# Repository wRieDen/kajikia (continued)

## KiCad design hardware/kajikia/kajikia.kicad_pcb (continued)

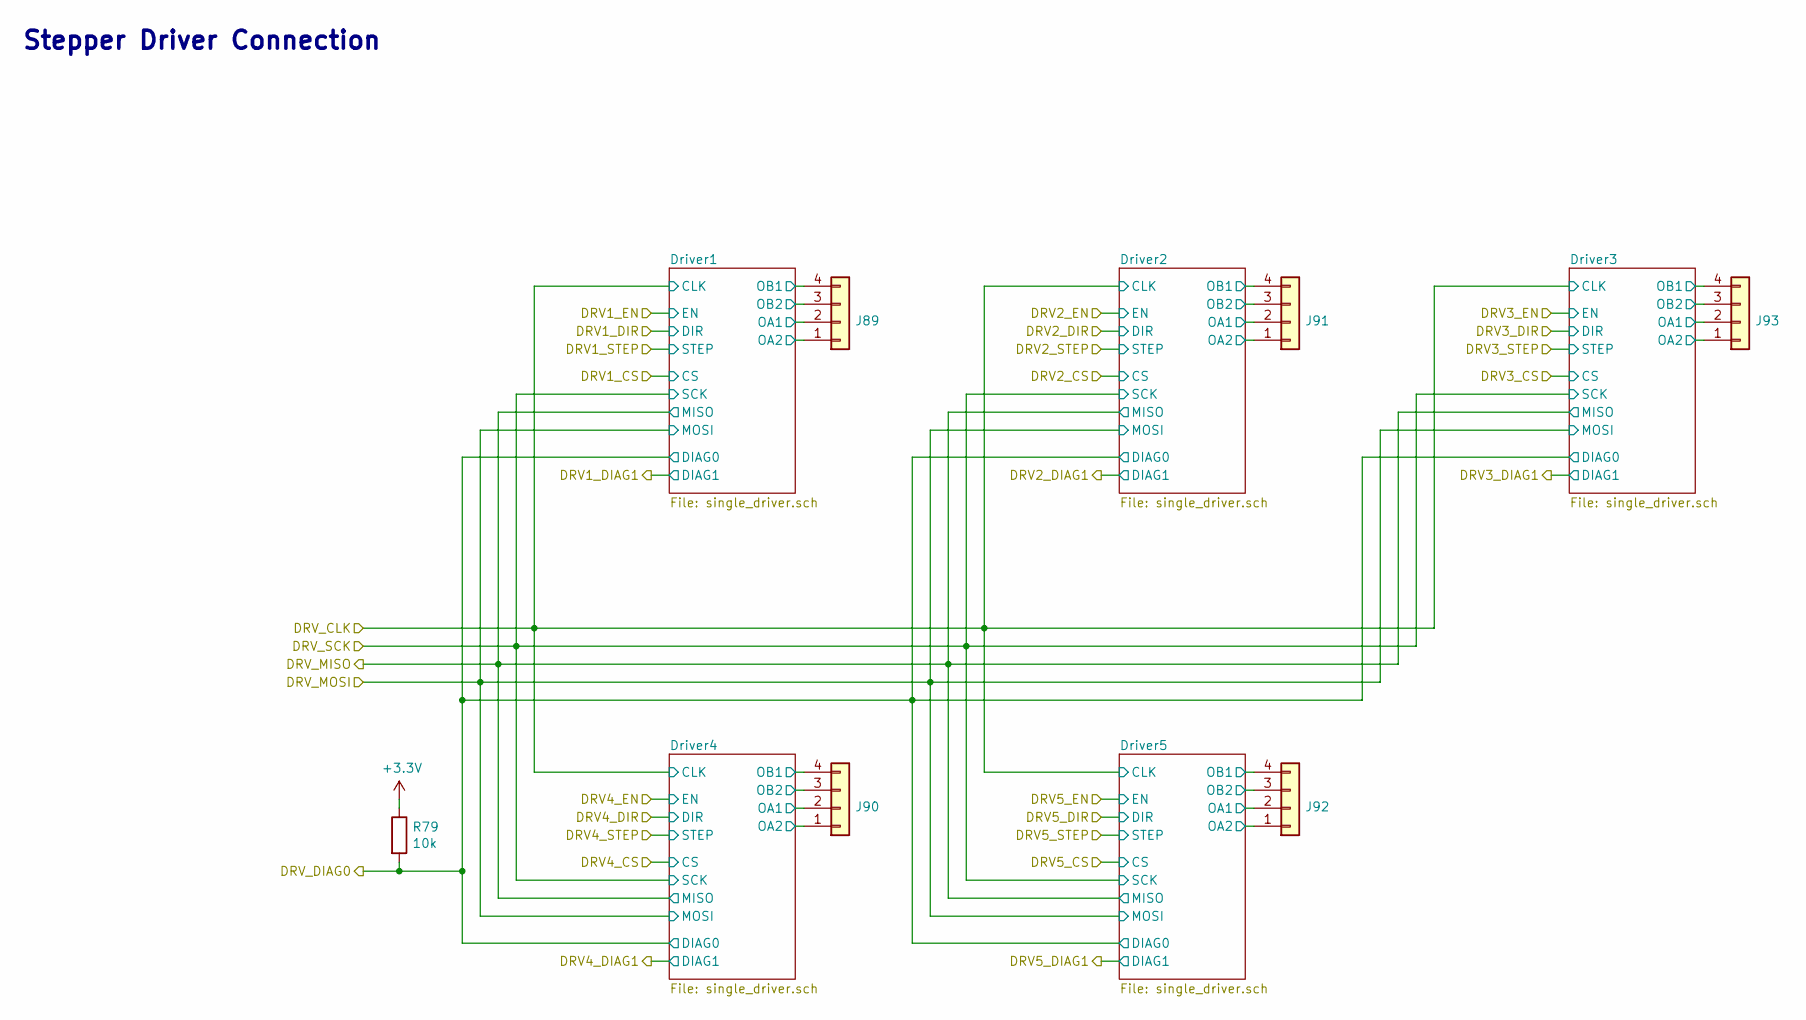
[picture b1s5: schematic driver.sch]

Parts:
J89, J90, J91, J92, J93: Conn_01x04; JST_XH_4P
R79: 10k; 0603_RES

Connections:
+3V3: R79.1; also elsewhere on the board
/Stepper Driver/DRV_DIAG0: R79.2; also elsewhere on the board
/Stepper Driver/Driver1/OA1: J89.2; also elsewhere on the board
/Stepper Driver/Driver1/OA2: J89.1; also elsewhere on the board
/Stepper Driver/Driver1/OB1: J89.4; also elsewhere on the board
/Stepper Driver/Driver1/OB2: J89.3; also elsewhere on the board
/Stepper Driver/Driver2/OA1: J91.2; also elsewhere on the board
/Stepper Driver/Driver2/OA2: J91.1; also elsewhere on the board
/Stepper Driver/Driver2/OB1: J91.4; also elsewhere on the board
/Stepper Driver/Driver2/OB2: J91.3; also elsewhere on the board
/Stepper Driver/Driver3/OA1: J93.2; also elsewhere on the board
/Stepper Driver/Driver3/OA2: J93.1; also elsewhere on the board
/Stepper Driver/Driver3/OB1: J93.4; also elsewhere on the board
/Stepper Driver/Driver3/OB2: J93.3; also elsewhere on the board
/Stepper Driver/Driver4/OA1: J90.2; also elsewhere on the board
/Stepper Driver/Driver4/OA2: J90.1; also elsewhere on the board
/Stepper Driver/Driver4/OB1: J90.4; also elsewhere on the board
/Stepper Driver/Driver4/OB2: J90.3; also elsewhere on the board
/Stepper Driver/Driver5/OA1: J92.2; also elsewhere on the board
/Stepper Driver/Driver5/OA2: J92.1; also elsewhere on the board
/Stepper Driver/Driver5/OB1: J92.4; also elsewhere on the board
/Stepper Driver/Driver5/OB2: J92.3; also elsewhere on the board

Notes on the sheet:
Stepper Driver Connection

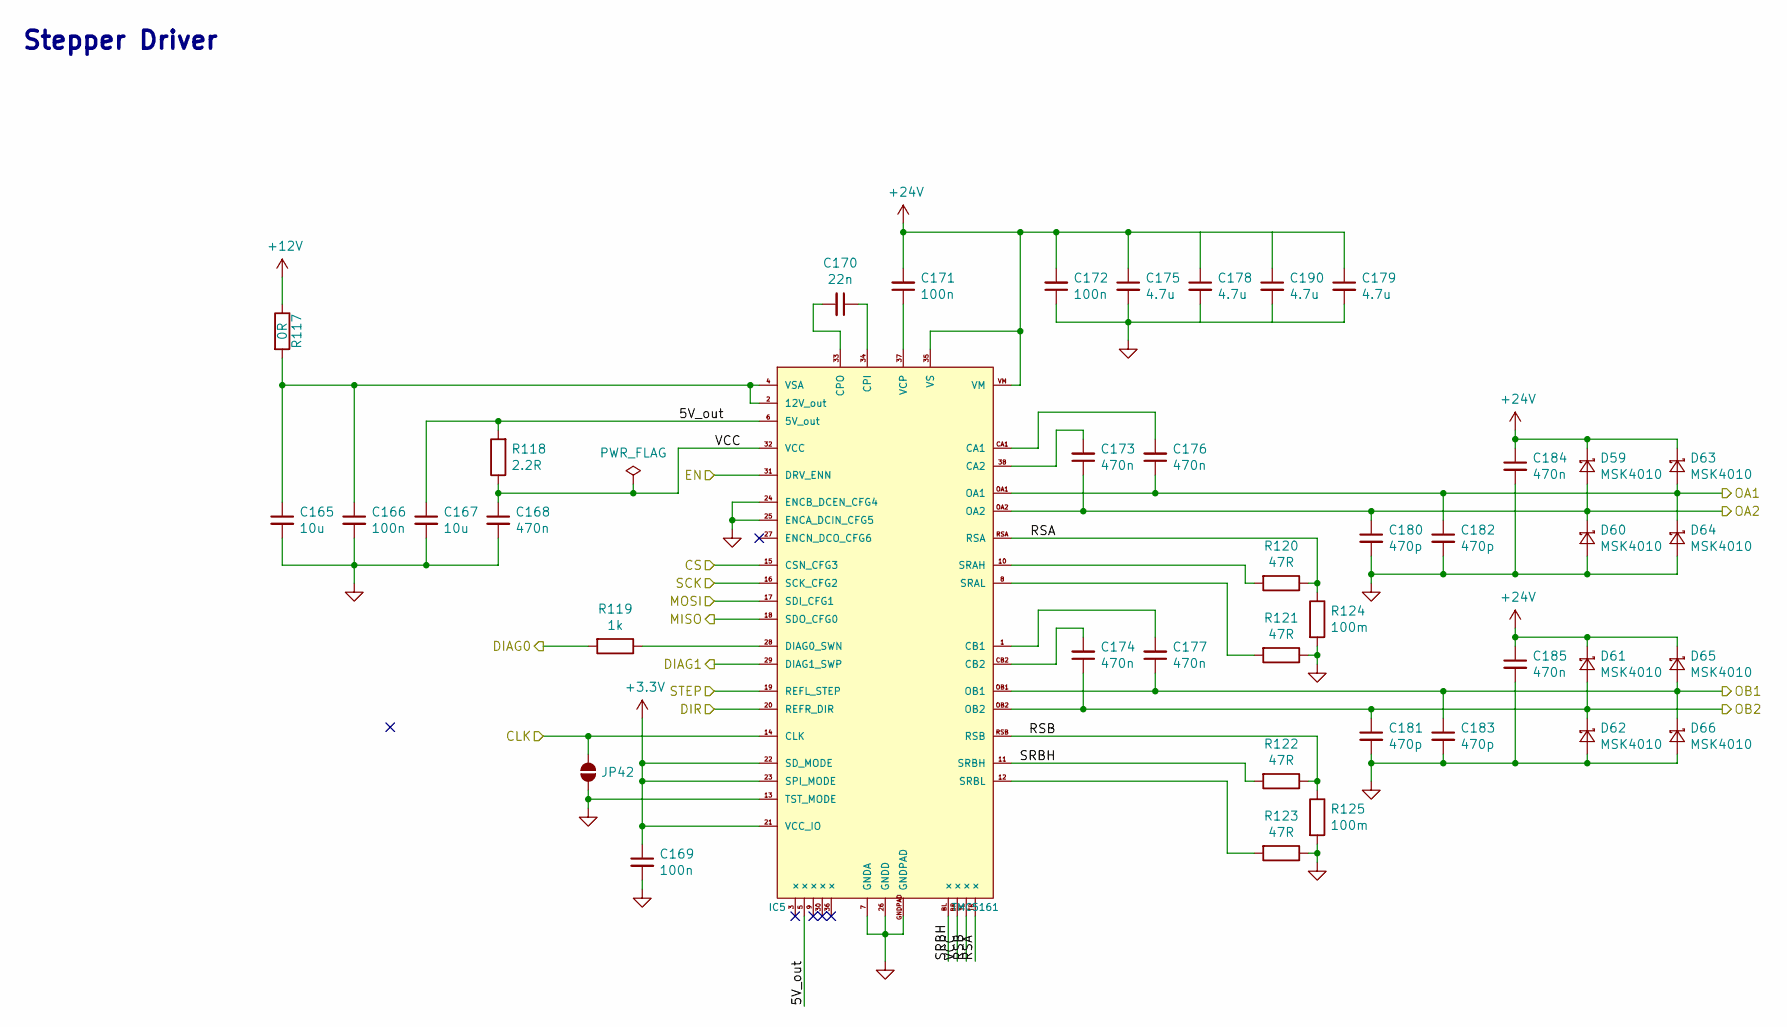
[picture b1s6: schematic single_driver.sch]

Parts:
C81, C83: 10u; 0603_CAP
C82, C85, C87, C88: 100n; 0603_CAP
C84, C89, C90, C92, C93, C100, C101: 470n; 0603_CAP
C86: 22n; 0603_CAP
C91, C94, C95, C186: 4.7u; 1210_CAP
C96, C97, C98, C99: 470p; 0603_CAP
D27, D28, D29, D30, D31, D32, D33, D34: MSK4010; SOD-523_DIODE
IC1: TMC5161; QFN42L
JP38: SolderJumper_2_Open; Solder Jumper 2P
R81: 0R; 0603_RES
R82: 2.2R; 0603_RES
R83: 1k; 0603_RES
R84, R85, R86, R87: 47R; 0603_RES
R88, R89: 100m; 1206_RES

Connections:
+3V3: C85.1, IC1.21 (VCC_IO), IC1.22 (SD_MODE), IC1.23 (SPI_MODE); also elsewhere on the board
+12V: R81.1; also elsewhere on the board
+24V: C87.2, C88.2, C91.1, C94.1, C95.1, C100.1, C101.1, C186.1, D27.1 (K), D29.1 (K), D31.1 (K), D33.1 (K), IC1.35 (VS), IC1.VM; also elsewhere on the board
/DRV1_CS: IC1.15 (CSN_CFG3); also elsewhere on the board
/DRV1_DIR: IC1.20 (REFR_DIR); also elsewhere on the board
/DRV1_EN: IC1.31 (DRV_ENN); also elsewhere on the board
/DRV1_STEP: IC1.19 (REFL_STEP); also elsewhere on the board
/DRV_CLK: IC1.14 (CLK), JP38.1 (A); also elsewhere on the board
/DRV_MISO: IC1.18 (SDO_CFG0); also elsewhere on the board
/DRV_MOSI: IC1.17 (SDI_CFG1); also elsewhere on the board
/DRV_SCK: IC1.16 (SCK_CFG2); also elsewhere on the board
/Stepper Driver/DRV1_DIAG1: IC1.29 (DIAG1_SWP); also elsewhere on the board
/Stepper Driver/DRV_DIAG0: R83.2; also elsewhere on the board
/Stepper Driver/Driver1/5V_out: C83.1, IC1.5 (×), IC1.6 (5V_out), R82.2
/Stepper Driver/Driver1/OA1: C92.1, C98.1, D31.2 (A), D32.1 (K), IC1.OA1; also elsewhere on the board
/Stepper Driver/Driver1/OA2: C89.1, C96.1, D27.2 (A), D28.1 (K), IC1.OA2; also elsewhere on the board
/Stepper Driver/Driver1/OB1: C93.1, C99.1, D33.2 (A), D34.1 (K), IC1.OB1; also elsewhere on the board
/Stepper Driver/Driver1/OB2: C90.1, C97.1, D29.2 (A), D30.1 (K), IC1.OB2; also elsewhere on the board
/Stepper Driver/Driver1/RSA: IC1.RSA, IC1.TR (×), R84.1, R88.1
/Stepper Driver/Driver1/RSB: IC1.RSB, IC1.TL (×), R86.1, R89.1
/Stepper Driver/Driver1/SRBH: IC1.11 (SRBH), IC1.BL (×), R86.2
/Stepper Driver/Driver1/VCC: C84.1, IC1.32 (VCC), IC1.BR (×), R82.1
GND: C81.2, C82.2, C83.2, C84.2, C85.2, C88.1, C91.2, C94.2, C95.2, C96.2, C97.2, C98.2, C99.2, C100.2, C101.2, C186.2, D28.2 (A), D30.2 (A), D32.2 (A), D34.2 (A), IC1.7 (GNDA), IC1.13 (TST_MODE), IC1.24 (ENCB_DCEN_CFG4), IC1.25 (ENCA_DCIN_CFG5), IC1.26 (GNDD), IC1.GNDPAD, JP38.2 (B), R85.1, R87.1, R88.2, R89.2; also elsewhere on the board
unnamed: C81.1, C82.1, IC1.2 (12V_out), IC1.4 (VSA), R81.2
unnamed: C86.1, IC1.34 (CPI)
unnamed: C86.2, IC1.33 (CPO)
unnamed: C87.1, IC1.37 (VCP)
unnamed: C89.2, IC1.38 (CA2)
unnamed: C90.2, IC1.CB2
unnamed: C92.2, IC1.CA1
unnamed: C93.2, IC1.1 (CB1)
unnamed: IC1.8 (SRAL), R85.2
unnamed: IC1.10 (SRAH), R84.2
unnamed: IC1.12 (SRBL), R87.2
unnamed: IC1.28 (DIAG0_SWN), R83.1

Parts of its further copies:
C102, C104, C123, C125, C144, C146, C165, C167: 10u; 0603_CAP
C103, C106, C108, C109, C124, C127, C129, C130, C145, C148, C150, C151, C166, C169, C171, C172: 100n; 0603_CAP
C105, C110, C111, C113, C114, C121, C122, C126, C131, C132, C134, C135, C142, C143, C147, C152, C153, C155, C156, C163, C164, C168, C173, C174, C176, C177, C184, C185: 470n; 0603_CAP
C107, C128, C149, C170: 22n; 0603_CAP
C112, C115, C116, C133, C136, C137, C154, C157, C158, C175, C178, C179, C187, C188, C189, C190: 4.7u; 1210_CAP
C117, C118, C119, C120, C138, C139, C140, C141, C159, C160, C161, C162, C180, C181, C182, C183: 470p; 0603_CAP
D35, D36, D37, D38, D39, D40, D41, D42, D43, D44, D45, D46, D47, D48, D49, D50, D51, D52, D53, D54, D55, D56, D57, D58, D59, D60, D61, D62, D63, D64, D65, D66: MSK4010; SOD-523_DIODE
IC2, IC3, IC4, IC5: TMC5161; QFN42L
JP39, JP40, JP41, JP42: SolderJumper_2_Open; Solder Jumper 2P
R90, R99, R108, R117: 0R; 0603_RES
R91, R100, R109, R118: 2.2R; 0603_RES
R92, R101, R110, R119: 1k; 0603_RES
R93, R94, R95, R96, R102, R103, R104, R105, R111, R112, R113, R114, R120, R121, R122, R123: 47R; 0603_RES
R97, R98, R106, R107, R115, R116, R124, R125: 100m; 1206_RES

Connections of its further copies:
+3V3: C106.1, C127.1, C148.1, C169.1, IC2.21 (VCC_IO), IC2.22 (SD_MODE), IC2.23 (SPI_MODE), IC3.21 (VCC_IO), IC3.22 (SD_MODE), IC3.23 (SPI_MODE), IC4.21 (VCC_IO), IC4.22 (SD_MODE), IC4.23 (SPI_MODE), IC5.21 (VCC_IO), IC5.22 (SD_MODE), IC5.23 (SPI_MODE); also elsewhere on the board
+12V: R90.1, R99.1, R108.1, R117.1; also elsewhere on the board
+24V: C108.2, C109.2, C112.1, C115.1, C116.1, C121.1, C122.1, C129.2, C130.2, C133.1, C136.1, C137.1, C142.1, C143.1, C150.2, C151.2, C154.1, C157.1, C158.1, C163.1, C164.1, C171.2, C172.2, C175.1, C178.1, C179.1, C184.1, C185.1, C187.1, C188.1, C189.1, C190.1, D35.1 (K), D37.1 (K), D39.1 (K), D41.1 (K), D43.1 (K), D45.1 (K), D47.1 (K), D49.1 (K), D51.1 (K), D53.1 (K), D55.1 (K), D57.1 (K), D59.1 (K), D61.1 (K), D63.1 (K), D65.1 (K), IC2.35 (VS), IC2.VM, IC3.35 (VS), IC3.VM, IC4.35 (VS), IC4.VM, IC5.35 (VS), IC5.VM; also elsewhere on the board
/DRV2_CS: IC2.15 (CSN_CFG3); also elsewhere on the board
/DRV2_DIR: IC2.20 (REFR_DIR); also elsewhere on the board
/DRV2_EN: IC2.31 (DRV_ENN); also elsewhere on the board
/DRV2_STEP: IC2.19 (REFL_STEP); also elsewhere on the board
/DRV3_CS: IC3.15 (CSN_CFG3); also elsewhere on the board
/DRV3_DIR: IC3.20 (REFR_DIR); also elsewhere on the board
/DRV3_EN: IC3.31 (DRV_ENN); also elsewhere on the board
/DRV3_STEP: IC3.19 (REFL_STEP); also elsewhere on the board
/DRV4_CS: IC4.15 (CSN_CFG3); also elsewhere on the board
/DRV4_DIR: IC4.20 (REFR_DIR); also elsewhere on the board
/DRV4_EN: IC4.31 (DRV_ENN); also elsewhere on the board
/DRV4_STEP: IC4.19 (REFL_STEP); also elsewhere on the board
/DRV_CLK: IC2.14 (CLK), IC3.14 (CLK), IC4.14 (CLK), IC5.14 (CLK), JP39.1 (A), JP40.1 (A), JP41.1 (A), JP42.1 (A); also elsewhere on the board
/DRV_MISO: IC2.18 (SDO_CFG0), IC3.18 (SDO_CFG0), IC4.18 (SDO_CFG0), IC5.18 (SDO_CFG0); also elsewhere on the board
/DRV_MOSI: IC2.17 (SDI_CFG1), IC3.17 (SDI_CFG1), IC4.17 (SDI_CFG1), IC5.17 (SDI_CFG1); also elsewhere on the board
/DRV_SCK: IC2.16 (SCK_CFG2), IC3.16 (SCK_CFG2), IC4.16 (SCK_CFG2), IC5.16 (SCK_CFG2); also elsewhere on the board
/Stepper Driver/DRV2_DIAG1: IC2.29 (DIAG1_SWP); also elsewhere on the board
/Stepper Driver/DRV3_DIAG1: IC3.29 (DIAG1_SWP); also elsewhere on the board
/Stepper Driver/DRV4_DIAG1: IC4.29 (DIAG1_SWP); also elsewhere on the board
/Stepper Driver/DRV5_CS: IC5.15 (CSN_CFG3); also elsewhere on the board
/Stepper Driver/DRV5_DIAG1: IC5.29 (DIAG1_SWP); also elsewhere on the board
/Stepper Driver/DRV5_DIR: IC5.20 (REFR_DIR); also elsewhere on the board
/Stepper Driver/DRV5_EN: IC5.31 (DRV_ENN); also elsewhere on the board
/Stepper Driver/DRV5_STEP: IC5.19 (REFL_STEP); also elsewhere on the board
/Stepper Driver/DRV_DIAG0: R92.2, R101.2, R110.2, R119.2; also elsewhere on the board
/Stepper Driver/Driver2/5V_out: C104.1, IC2.5 (×), IC2.6 (5V_out), R91.2
/Stepper Driver/Driver2/OA1: C113.1, C119.1, D39.2 (A), D40.1 (K), IC2.OA1; also elsewhere on the board
/Stepper Driver/Driver2/OA2: C110.1, C117.1, D35.2 (A), D36.1 (K), IC2.OA2; also elsewhere on the board
/Stepper Driver/Driver2/OB1: C114.1, C120.1, D41.2 (A), D42.1 (K), IC2.OB1; also elsewhere on the board
/Stepper Driver/Driver2/OB2: C111.1, C118.1, D37.2 (A), D38.1 (K), IC2.OB2; also elsewhere on the board
/Stepper Driver/Driver2/RSA: IC2.RSA, IC2.TR (×), R93.1, R97.1
/Stepper Driver/Driver2/RSB: IC2.RSB, IC2.TL (×), R95.1, R98.1
/Stepper Driver/Driver2/SRBH: IC2.11 (SRBH), IC2.BL (×), R95.2
/Stepper Driver/Driver2/VCC: C105.1, IC2.32 (VCC), IC2.BR (×), R91.1
/Stepper Driver/Driver3/5V_out: C125.1, IC3.5 (×), IC3.6 (5V_out), R100.2
/Stepper Driver/Driver3/OA1: C134.1, C140.1, D47.2 (A), D48.1 (K), IC3.OA1; also elsewhere on the board
/Stepper Driver/Driver3/OA2: C131.1, C138.1, D43.2 (A), D44.1 (K), IC3.OA2; also elsewhere on the board
/Stepper Driver/Driver3/OB1: C135.1, C141.1, D49.2 (A), D50.1 (K), IC3.OB1; also elsewhere on the board
/Stepper Driver/Driver3/OB2: C132.1, C139.1, D45.2 (A), D46.1 (K), IC3.OB2; also elsewhere on the board
/Stepper Driver/Driver3/RSA: IC3.RSA, IC3.TR (×), R102.1, R106.1
/Stepper Driver/Driver3/RSB: IC3.RSB, IC3.TL (×), R104.1, R107.1
/Stepper Driver/Driver3/SRBH: IC3.11 (SRBH), IC3.BL (×), R104.2
/Stepper Driver/Driver3/VCC: C126.1, IC3.32 (VCC), IC3.BR (×), R100.1
/Stepper Driver/Driver4/5V_out: C146.1, IC4.5 (×), IC4.6 (5V_out), R109.2
/Stepper Driver/Driver4/OA1: C155.1, C161.1, D55.2 (A), D56.1 (K), IC4.OA1; also elsewhere on the board
/Stepper Driver/Driver4/OA2: C152.1, C159.1, D51.2 (A), D52.1 (K), IC4.OA2; also elsewhere on the board
/Stepper Driver/Driver4/OB1: C156.1, C162.1, D57.2 (A), D58.1 (K), IC4.OB1; also elsewhere on the board
/Stepper Driver/Driver4/OB2: C153.1, C160.1, D53.2 (A), D54.1 (K), IC4.OB2; also elsewhere on the board
/Stepper Driver/Driver4/RSA: IC4.RSA, IC4.TR (×), R111.1, R115.1
/Stepper Driver/Driver4/RSB: IC4.RSB, IC4.TL (×), R113.1, R116.1
/Stepper Driver/Driver4/SRBH: IC4.11 (SRBH), IC4.BL (×), R113.2
/Stepper Driver/Driver4/VCC: C147.1, IC4.32 (VCC), IC4.BR (×), R109.1
/Stepper Driver/Driver5/5V_out: C167.1, IC5.5 (×), IC5.6 (5V_out), R118.2
/Stepper Driver/Driver5/OA1: C176.1, C182.1, D63.2 (A), D64.1 (K), IC5.OA1; also elsewhere on the board
/Stepper Driver/Driver5/OA2: C173.1, C180.1, D59.2 (A), D60.1 (K), IC5.OA2; also elsewhere on the board
/Stepper Driver/Driver5/OB1: C177.1, C183.1, D65.2 (A), D66.1 (K), IC5.OB1; also elsewhere on the board
/Stepper Driver/Driver5/OB2: C174.1, C181.1, D61.2 (A), D62.1 (K), IC5.OB2; also elsewhere on the board
/Stepper Driver/Driver5/RSA: IC5.RSA, IC5.TR (×), R120.1, R124.1
/Stepper Driver/Driver5/RSB: IC5.RSB, IC5.TL (×), R122.1, R125.1
/Stepper Driver/Driver5/SRBH: IC5.11 (SRBH), IC5.BL (×), R122.2
/Stepper Driver/Driver5/VCC: C168.1, IC5.32 (VCC), IC5.BR (×), R118.1
GND: C102.2, C103.2, C104.2, C105.2, C106.2, C109.1, C112.2, C115.2, C116.2, C117.2, C118.2, C119.2, C120.2, C121.2, C122.2, C123.2, C124.2, C125.2, C126.2, C127.2, C130.1, C133.2, C136.2, C137.2, C138.2, C139.2, C140.2, C141.2, C142.2, C143.2, C144.2, C145.2, C146.2, C147.2, C148.2, C151.1, C154.2, C157.2, C158.2, C159.2, C160.2, C161.2, C162.2, C163.2, C164.2, C165.2, C166.2, C167.2, C168.2, C169.2, C172.1, C175.2, C178.2, C179.2, C180.2, C181.2, C182.2, C183.2, C184.2, C185.2, C187.2, C188.2, C189.2, C190.2, D36.2 (A), D38.2 (A), D40.2 (A), D42.2 (A), D44.2 (A), D46.2 (A), D48.2 (A), D50.2 (A), D52.2 (A), D54.2 (A), D56.2 (A), D58.2 (A), D60.2 (A), D62.2 (A), D64.2 (A), D66.2 (A), IC2.7 (GNDA), IC2.13 (TST_MODE), IC2.24 (ENCB_DCEN_CFG4), IC2.25 (ENCA_DCIN_CFG5), IC2.26 (GNDD), IC2.GNDPAD, IC3.7 (GNDA), IC3.13 (TST_MODE), IC3.24 (ENCB_DCEN_CFG4), IC3.25 (ENCA_DCIN_CFG5), IC3.26 (GNDD), IC3.GNDPAD, IC4.7 (GNDA), IC4.13 (TST_MODE), IC4.24 (ENCB_DCEN_CFG4), IC4.25 (ENCA_DCIN_CFG5), IC4.26 (GNDD), IC4.GNDPAD, IC5.7 (GNDA), IC5.13 (TST_MODE), IC5.24 (ENCB_DCEN_CFG4), IC5.25 (ENCA_DCIN_CFG5), IC5.26 (GNDD), IC5.GNDPAD, JP39.2 (B), JP40.2 (B), JP41.2 (B), JP42.2 (B), R94.1, R96.1, R97.2, R98.2, R103.1, R105.1, R106.2, R107.2, R112.1, R114.1, R115.2, R116.2, R121.1, R123.1, R124.2, R125.2; also elsewhere on the board
unnamed: C102.1, C103.1, IC2.2 (12V_out), IC2.4 (VSA), R90.2
unnamed: C107.1, IC2.34 (CPI)
unnamed: C107.2, IC2.33 (CPO)
unnamed: C108.1, IC2.37 (VCP)
unnamed: C110.2, IC2.38 (CA2)
unnamed: C111.2, IC2.CB2
unnamed: C113.2, IC2.CA1
unnamed: C114.2, IC2.1 (CB1)
unnamed: C123.1, C124.1, IC3.2 (12V_out), IC3.4 (VSA), R99.2
unnamed: C128.1, IC3.34 (CPI)
unnamed: C128.2, IC3.33 (CPO)
unnamed: C129.1, IC3.37 (VCP)
unnamed: C131.2, IC3.38 (CA2)
unnamed: C132.2, IC3.CB2
unnamed: C134.2, IC3.CA1
unnamed: C135.2, IC3.1 (CB1)
unnamed: C144.1, C145.1, IC4.2 (12V_out), IC4.4 (VSA), R108.2
unnamed: C149.1, IC4.34 (CPI)
unnamed: C149.2, IC4.33 (CPO)
unnamed: C150.1, IC4.37 (VCP)
unnamed: C152.2, IC4.38 (CA2)
unnamed: C153.2, IC4.CB2
unnamed: C155.2, IC4.CA1
unnamed: C156.2, IC4.1 (CB1)
unnamed: C165.1, C166.1, IC5.2 (12V_out), IC5.4 (VSA), R117.2
unnamed: C170.1, IC5.34 (CPI)
unnamed: C170.2, IC5.33 (CPO)
unnamed: C171.1, IC5.37 (VCP)
unnamed: C173.2, IC5.38 (CA2)
unnamed: C174.2, IC5.CB2
unnamed: C176.2, IC5.CA1
unnamed: C177.2, IC5.1 (CB1)
unnamed: IC2.8 (SRAL), R94.2
unnamed: IC2.10 (SRAH), R93.2
unnamed: IC2.12 (SRBL), R96.2
unnamed: IC2.28 (DIAG0_SWN), R92.1
unnamed: IC3.8 (SRAL), R103.2
unnamed: IC3.10 (SRAH), R102.2
unnamed: IC3.12 (SRBL), R105.2
unnamed: IC3.28 (DIAG0_SWN), R101.1
unnamed: IC4.8 (SRAL), R112.2
unnamed: IC4.10 (SRAH), R111.2
unnamed: IC4.12 (SRBL), R114.2
unnamed: IC4.28 (DIAG0_SWN), R110.1
unnamed: IC5.8 (SRAL), R121.2
unnamed: IC5.10 (SRAH), R120.2
unnamed: IC5.12 (SRBL), R123.2
unnamed: IC5.28 (DIAG0_SWN), R119.1

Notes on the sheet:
Stepper Driver

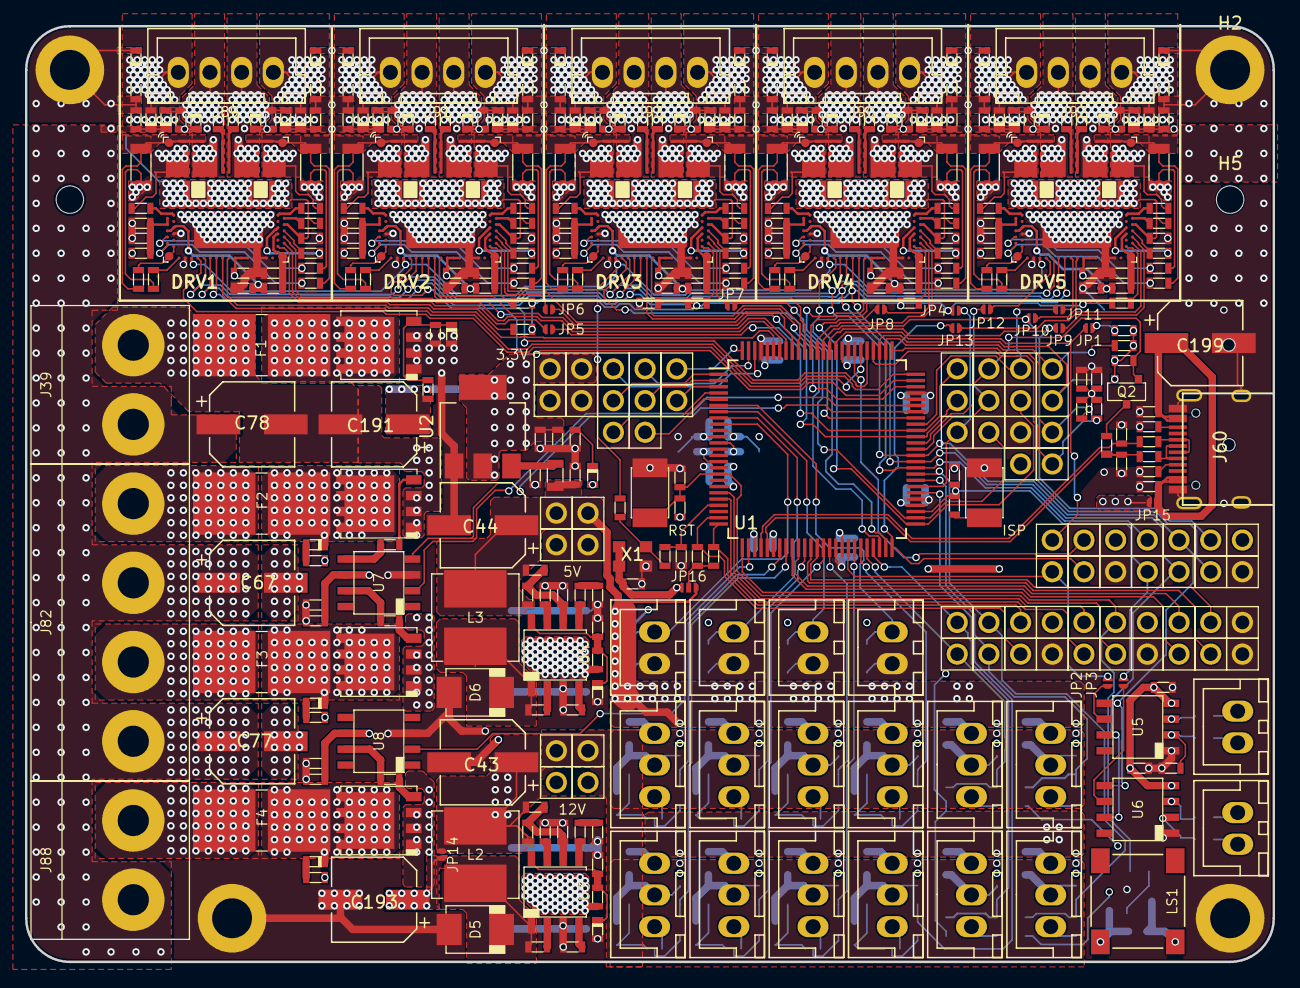
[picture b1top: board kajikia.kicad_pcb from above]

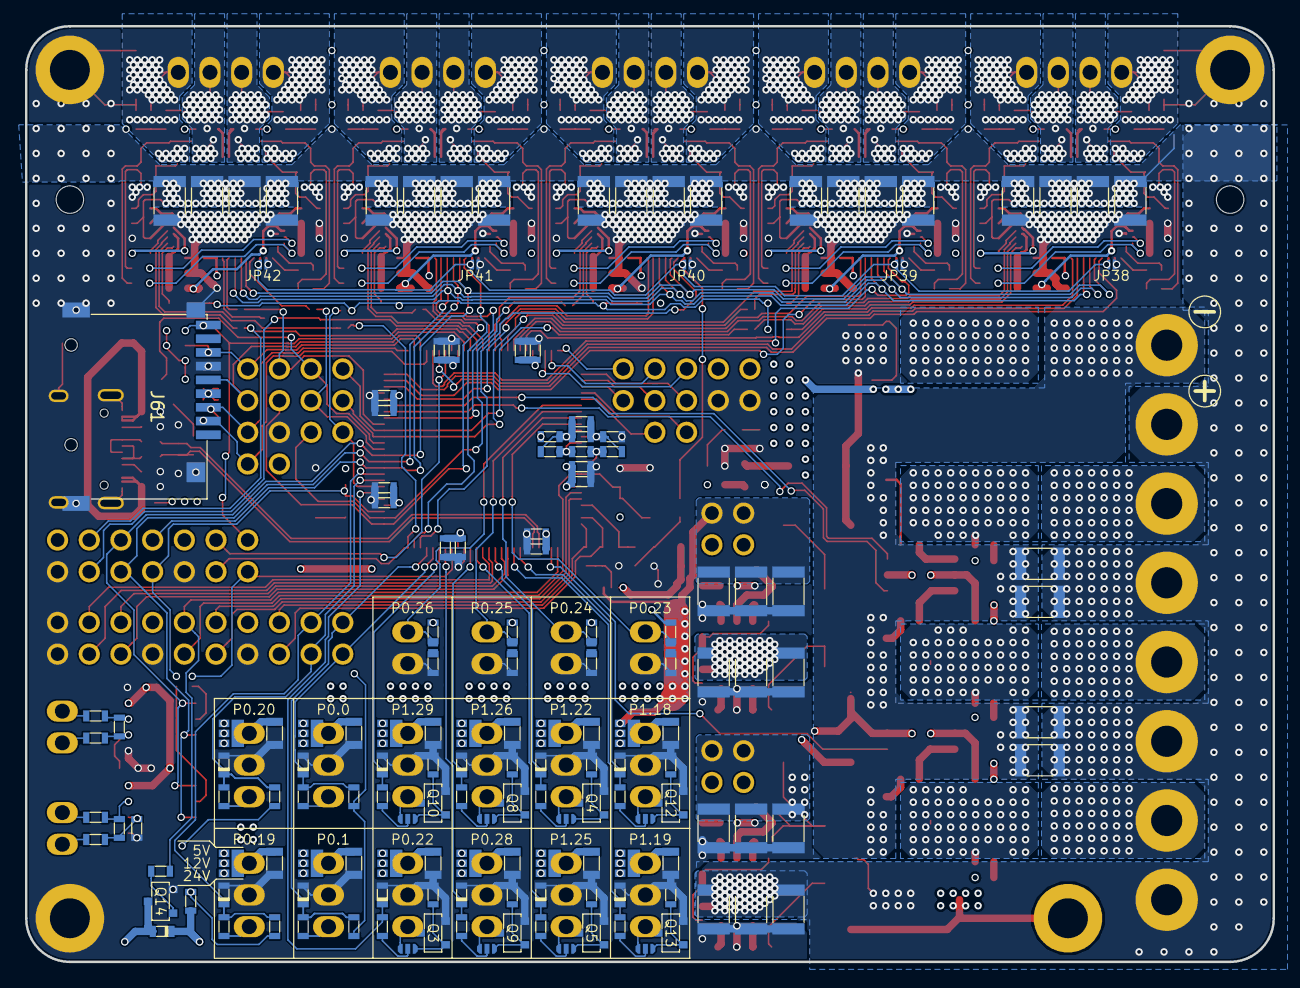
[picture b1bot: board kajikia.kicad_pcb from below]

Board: 4 copper layers, 100.0 x 75.0 mm, 567 parts (162 on the bottom side), 306 nets.

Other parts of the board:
H5, H6: MountingHole; MountingHole_2.2mm_M2_DIN965
ISP: 3x6mm; Switch_3x4mm
RST: 3x6mm; Switch_3x4mm

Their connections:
/RST: RST.1; also elsewhere on the board
GND: ISP.2, RST.2; also elsewhere on the board
unnamed 328: ISP.1; also elsewhere on the board

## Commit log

2018-05-12 tmc5130
2018-05-13 stm32h7
2018-05-18 hc, lc and protected ios
2018-05-20 reorder started
2018-05-20 reorder
2018-05-23 io assignments
2019-01-02 switch to tmc5161
2019-01-03 lpc, ios
2019-01-04 max6675, cleanup
2019-01-06 power
2019-01-06 fancy
2019-01-06 move power
2019-01-07 footprints
2019-01-07 layout test
2019-01-08 tmc layout
2019-01-09 before copy
2019-01-12 all driver
2019-01-12 driver polys
2019-01-15 fuses
2019-01-17 continue routing
2019-01-21 PCB V1
2019-01-23 added used footprint, models and symbols
2019-03-04 sheet description
